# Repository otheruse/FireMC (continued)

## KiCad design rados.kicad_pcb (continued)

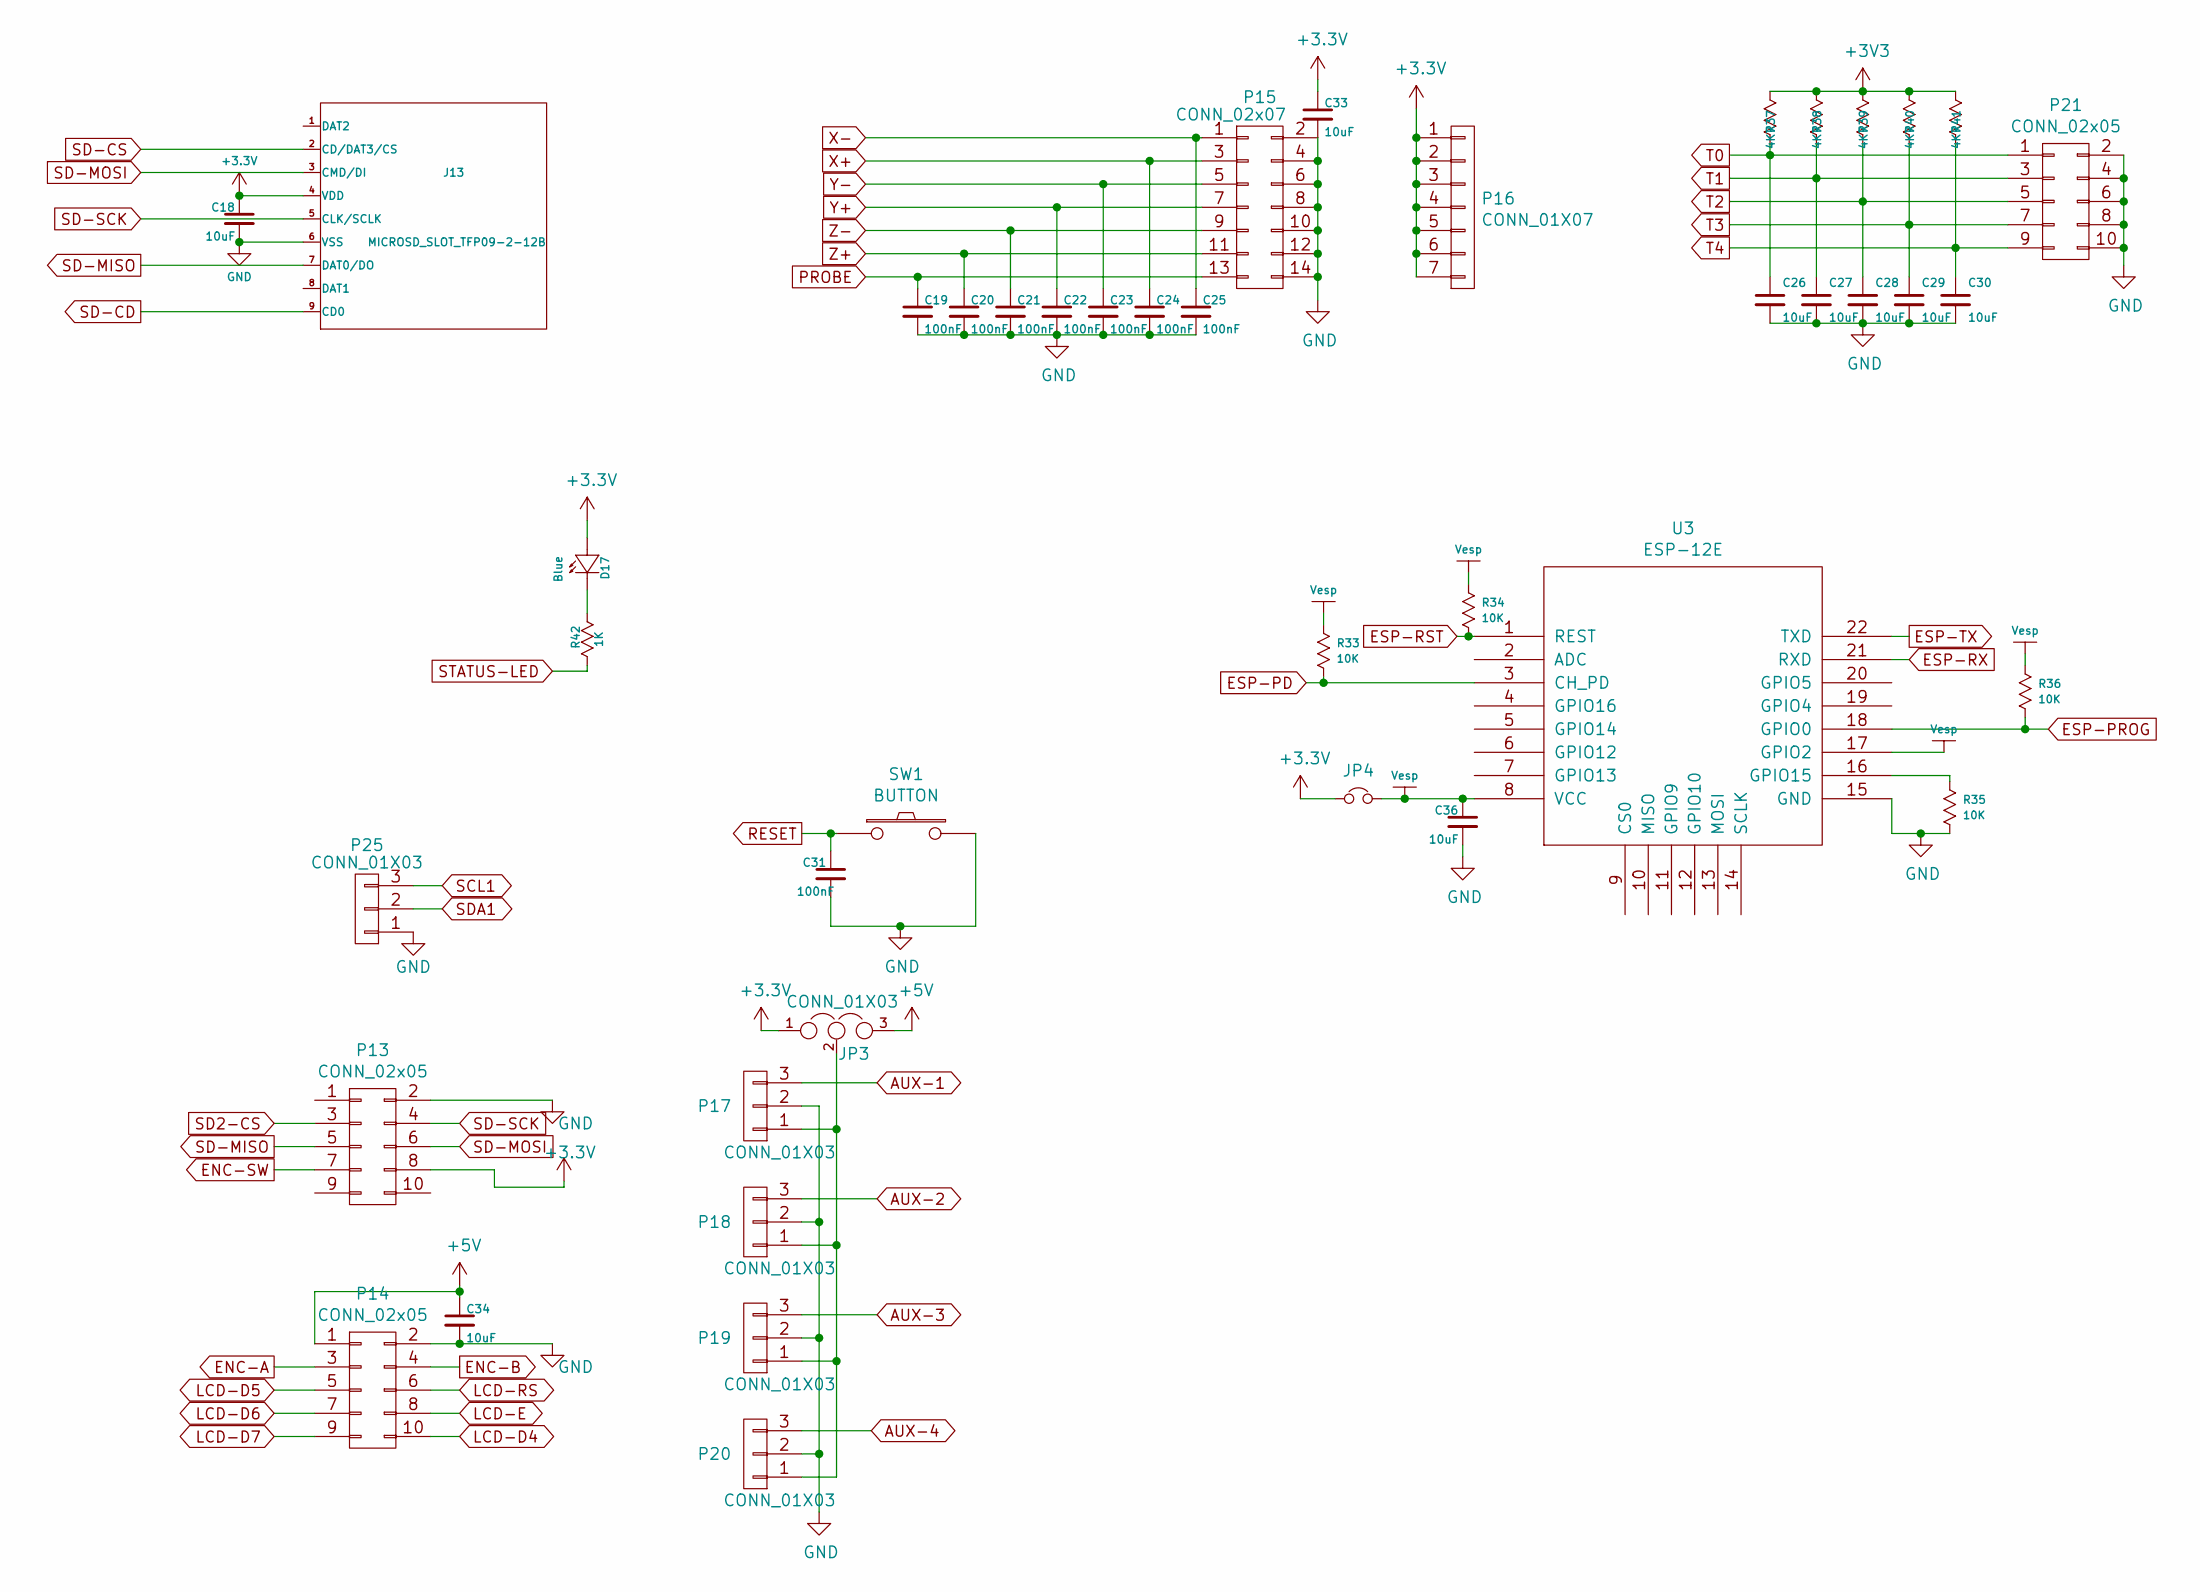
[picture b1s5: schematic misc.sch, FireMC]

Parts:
C18, C26, C27, C28, C29, C30, C33, C34, C36: 10uF; C_0805; VoltageRating 6.3V
C19, C20, C21, C22, C23, C24, C25, C31: 100nF; C_0603; VoltageRating 16V
D17: Blue; LED-0603
J13: MICROSD_SLOT_TFP09-2-12B
JP3: CONN_01X03; CON_HDR_1x3_2.54mm
JP4: CONN_01X02; CON_HDR_1x2_2.54mm
P13, P14, P21: CONN_02x05; CON_HDR_2x5_2.54mm
P15: CONN_02x07; CON_HDR_2x7_2.54mm
P16: CONN_01X07; CON_HDR_1x7_2.54mm
P17, P18, P19, P20, P25: CONN_01X03; CON_HDR_1x3_2.54mm
R33, R34, R35, R36: 10K; R_0603
R37, R38, R39, R40, R41: 4K7; R_0603
R42: 1K; R_0603
SW1: BUTTON; BUTTON_PUSH_SMD_6x6mm
U3: ESP-12E

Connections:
+5V: C34.1, JP3.3, P14.1; also elsewhere on the board
AUX-1: P17.3; also elsewhere on the board
AUX-2: P18.3; also elsewhere on the board
AUX-3: P19.3; also elsewhere on the board
AUX-4: P20.3; also elsewhere on the board
ENC-A: P14.3; also elsewhere on the board
ENC-B: P14.4; also elsewhere on the board
ENC-SW: P13.7; also elsewhere on the board
ESP-PD: R33.2, U3.3 (CH_PD); also elsewhere on the board
ESP-PROG: R36.2, U3.18 (GPIO0); also elsewhere on the board
ESP-RST: R34.2, U3.1 (REST); also elsewhere on the board
ESP-RX: U3.21 (RXD); also elsewhere on the board
ESP-TX: U3.22 (TXD); also elsewhere on the board
GND: C18.2, C19.2, C20.2, C21.2, C22.2, C23.2, C24.2, C25.2, C26.2, C27.2, C28.2, C29.2, C30.2, C31.2, C33.2, C34.2, C36.2, J13.6 (VSS), P13.2, P14.2, P15.2, P15.4, P15.6, P15.8, P15.10, P15.12, P15.14, P17.2, P18.2, P19.2, P20.2, P21.2, P21.4, P21.6, P21.8, P21.10, P25.1, R35.2, SW1.2, U3.15 (GND); also elsewhere on the board
LCD-D4: P14.10; also elsewhere on the board
LCD-D5: P14.5; also elsewhere on the board
LCD-D6: P14.7; also elsewhere on the board
LCD-D7: P14.9; also elsewhere on the board
LCD-E: P14.8; also elsewhere on the board
LCD-RS: P14.6; also elsewhere on the board
unnamed: D17.2, R42.1
unnamed: JP3.2, P17.1, P18.1, P19.1, P20.1
unnamed: R35.1, U3.16 (GPIO15)
PROBE: C19.1, P15.13; also elsewhere on the board
RESET: C31.1, SW1.1; also elsewhere on the board
SCL1: P25.3; also elsewhere on the board
SD2-CS: P13.3; also elsewhere on the board
SD-CD: J13.9 (CD0)
SD-CS: J13.2 (CD/DAT3/CS); also elsewhere on the board
SD-MISO: J13.7 (DAT0/DO), P13.5; also elsewhere on the board
SD-MOSI: J13.3 (CMD/DI), P13.6; also elsewhere on the board
SD-SCK: J13.5 (CLK/SCLK), P13.4; also elsewhere on the board
SDA1: P25.2; also elsewhere on the board
STATUS-LED: R42.2; also elsewhere on the board
T0: C26.1, P21.1, R37.2; also elsewhere on the board
T1: C27.1, P21.3, R38.2; also elsewhere on the board
T2: C28.1, P21.5, R39.2; also elsewhere on the board
T3: C29.1, P21.7, R40.2; also elsewhere on the board
T4: C30.1, P21.9, R41.2; also elsewhere on the board
Vesp: C36.1, JP4.2, R33.1, R34.1, R36.1, U3.8 (VCC), U3.17 (GPIO2)
X+: C24.1, P15.3; also elsewhere on the board
X-: C25.1, P15.1; also elsewhere on the board
Y+: C22.1, P15.7; also elsewhere on the board
Y-: C23.1, P15.5; also elsewhere on the board
Z+: C20.1, P15.11; also elsewhere on the board
Z-: C21.1, P15.9; also elsewhere on the board

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
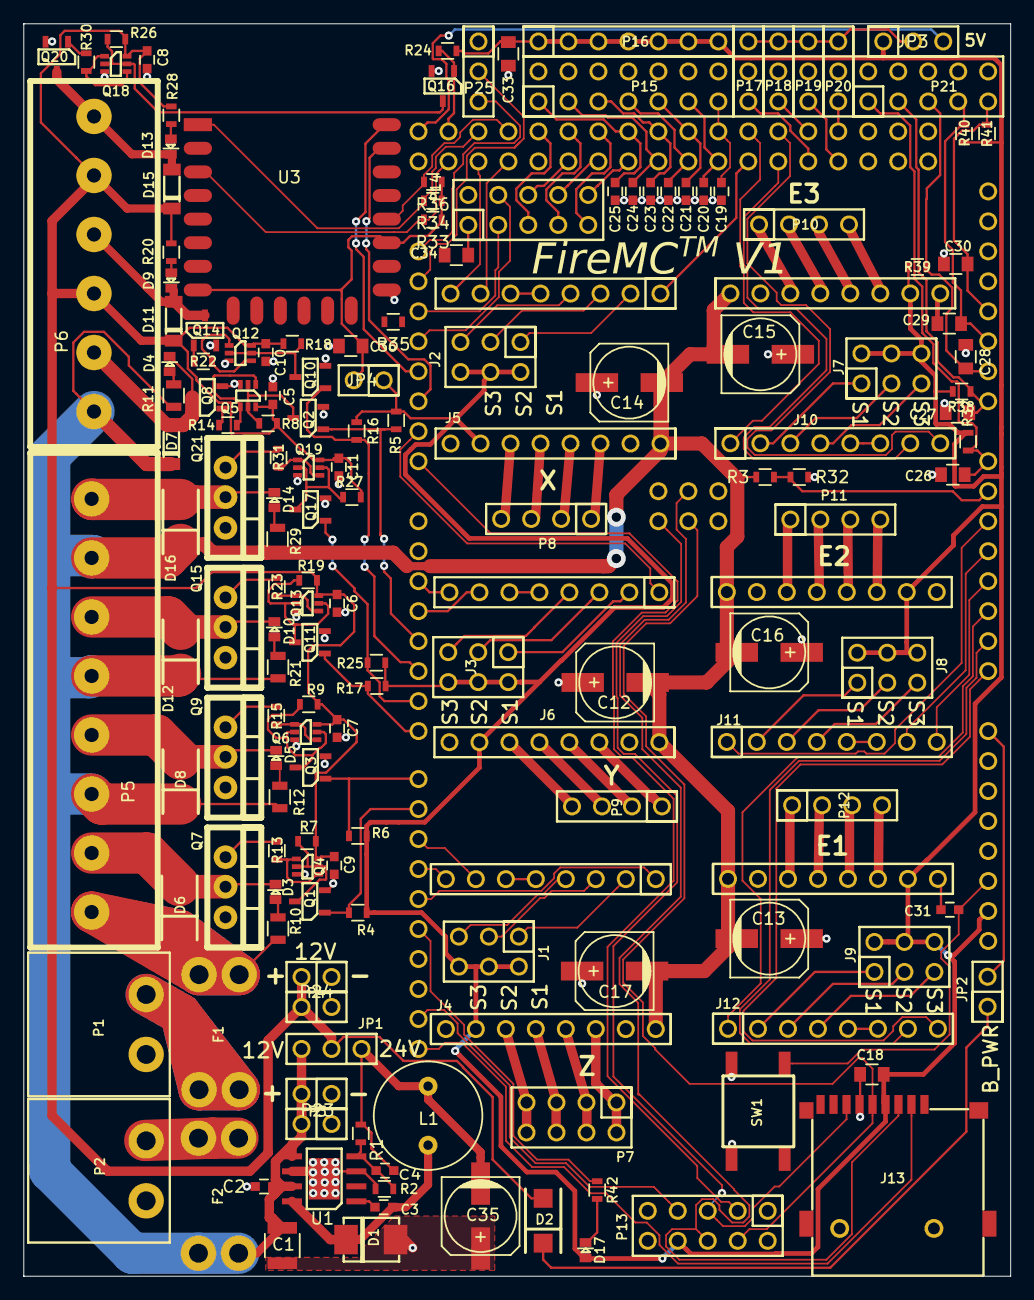
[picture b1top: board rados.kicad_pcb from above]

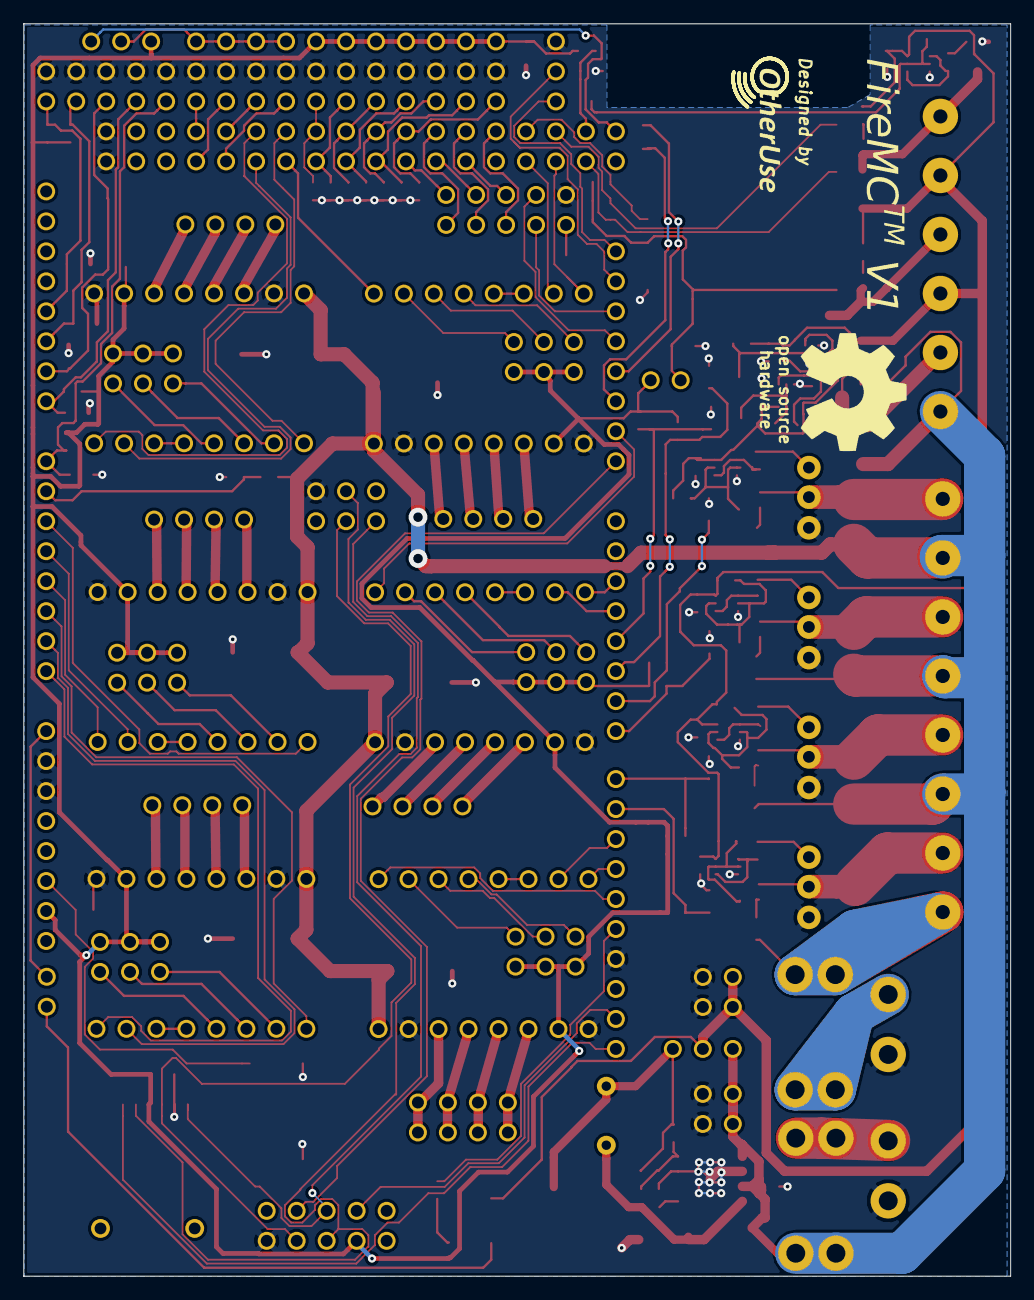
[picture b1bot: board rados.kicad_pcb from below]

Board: 2 copper layers, 83.6 x 106.1 mm, 166 parts (2 on the bottom side), 166 nets.

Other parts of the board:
svg2mod, svg2mod#2: G***; firemc-logo
svg2mod#3: G***; OtherUseLogo_medium

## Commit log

2016-01-05 RADOS initial version
2016-01-06 more schematics
2016-01-07 More schematics, some layout
2016-01-11 more placement and routing
2016-01-11 More routing
2016-01-12 Routing almost finished
2016-01-13 Added 3d models
2016-01-15 More 3d stuff
2016-01-15 cleanup
2016-01-16 fixed minor issue
2016-01-17 fixed some errors
2016-01-21 Silkcscreen placement
2016-02-10 - added wifi esp8266 - switched caps to smd - fixed dual transistor pinout bug
2016-02-11 Routing
2016-02-11 Lots of routing
2016-02-11 some refinements
2016-02-12 Replaced SMPS with ST ic
2016-02-12 Silk placement
2016-02-13 add to todo
2016-02-13 Moved heatbed io away from arduino led-output (D13)
2016-02-13 Updated todo
2016-02-14 More TODO
2016-02-15 - Some mosfets now can have hardware PWM - moved eeprom to i2c with arduino pull-ups
2016-02-16 Fixed some TODO's
2016-02-18 Added minimal arduino mega support
2016-02-19 Added some names/logo's on silkscreen
2016-02-19 Renamed schematics
2016-02-19 Added minimal README
2016-02-19 Added license
2016-02-22 Changed gate resistor values
2016-03-08 Added component specifications
2016-03-10 Added specifications and manufacturers to component attributes
2016-03-10 More specs
2016-03-17 - Fix si2318 pinout - Fix slot problem introduced with attribute changes
2016-03-18 Clearance around wifi power jumper
2016-03-24 fix analog and wifi
2016-03-24 Add pinout picture
2016-03-24 Added logo's that somehow disappeared
2016-05-28 Removed jumper in arduino power line: arduino is now always powered when FireMC is powered
2016-08-16 Rescued some symbols
